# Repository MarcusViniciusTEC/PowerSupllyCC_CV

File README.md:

# PowerSupllyCC_CV

layout fonte CC/CV, controlado por STM32F103 e display 128x64

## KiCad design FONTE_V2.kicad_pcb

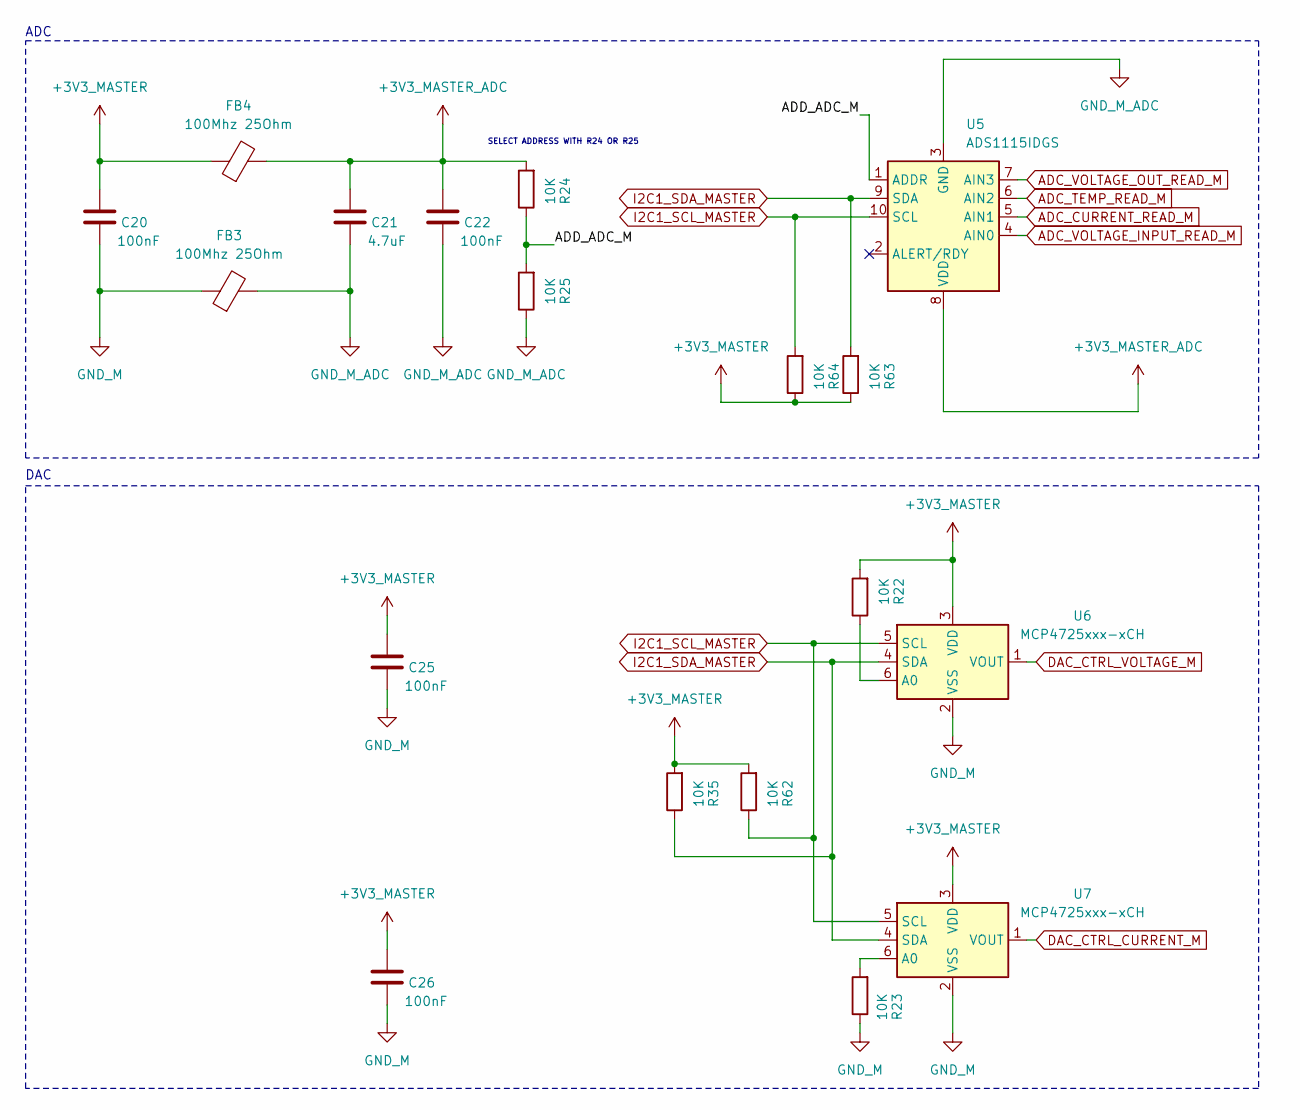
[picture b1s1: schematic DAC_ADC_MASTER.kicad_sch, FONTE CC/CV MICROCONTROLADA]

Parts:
C20, C22, C25, C26: 100nF; C_0805_2012Metric_Pad1.18x1.45mm_HandSolder
C21: 4.7uF; C_0805_2012Metric_Pad1.18x1.45mm_HandSolder
FB3, FB4: 100Mhz 25Ohm; L_0805_2012Metric_Pad1.15x1.40mm_HandSolder
R22, R23, R24, R25, R35, R62, R63, R64: 10K; R_0805_2012Metric_Pad1.20x1.40mm_HandSolder
U5: ADS1115IDGS; TSSOP-10_3x3mm_P0.5mm
U6, U7: MCP4725xxx-xCH; SOT-23-6

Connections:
+3V3_MASTER: C20.1, C25.1, C26.1, FB4.1, R22.2, R35.2, R62.2, R63.1, R64.1, U6.3 (VDD), U7.3 (VDD); also elsewhere on the board
+3V3_MASTER_ADC: C21.1, C22.1, FB4.2, R24.2, U5.8 (VDD)
/DAC_ADC_MASTER/ADD_ADC_M: R24.1, R25.2, U5.1 (ADDR)
ADC_CURRENT_READ_M: U5.5 (AIN1); also elsewhere on the board
ADC_TEMP_READ_M: U5.6 (AIN2); also elsewhere on the board
ADC_VOLTAGE_INPUT_READ_M: U5.4 (AIN0); also elsewhere on the board
ADC_VOLTAGE_OUT_READ_M: U5.7 (AIN3); also elsewhere on the board
DAC_CTRL_CURRENT_M: U7.1 (VOUT); also elsewhere on the board
DAC_CTRL_VOLTAGE_M: U6.1 (VOUT); also elsewhere on the board
GND_M_ADC: C21.2, C22.2, FB3.2, R25.1, U5.3 (GND)
I2C1_SCL_MASTER: R62.1, R64.2, U5.10 (SCL), U6.5 (SCL), U7.5 (SCL); also elsewhere on the board
I2C1_SDA_MASTER: R35.1, R63.2, U5.9 (SDA), U6.4 (SDA), U7.4 (SDA); also elsewhere on the board
unnamed: R22.1, U6.6 (A0)
unnamed: R23.2, U7.6 (A0)

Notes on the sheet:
SELECT ADDRESS WITH R24 OR R25
ADC
DAC

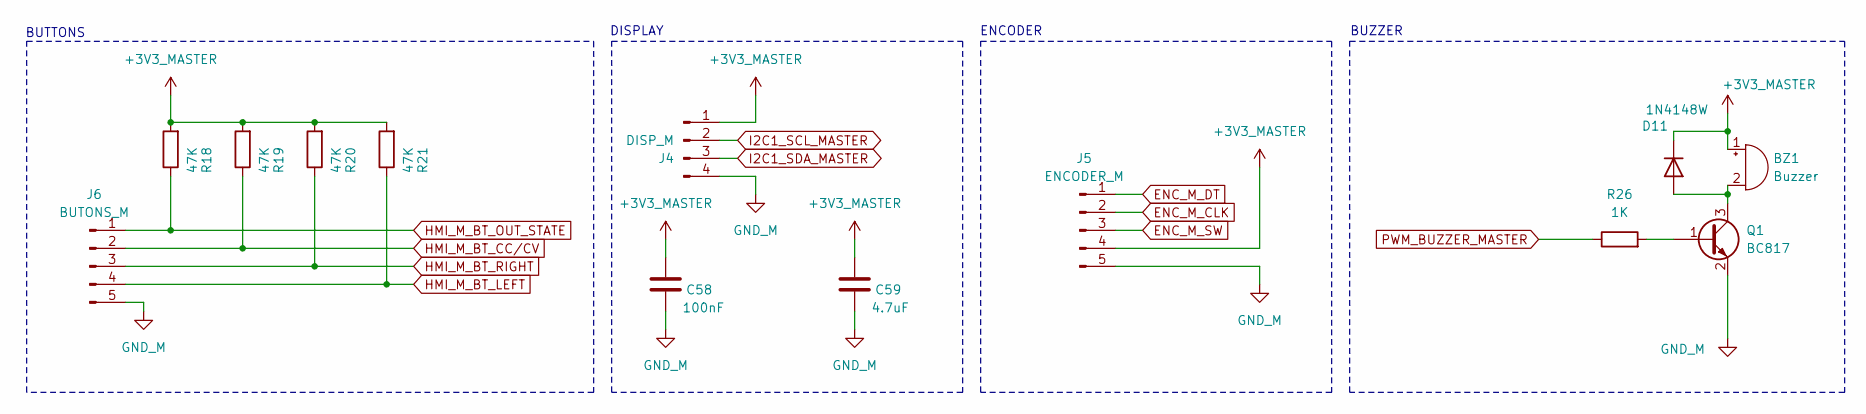
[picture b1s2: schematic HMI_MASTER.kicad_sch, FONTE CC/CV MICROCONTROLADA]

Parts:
BZ1: Buzzer; Buzzer_12x9.5RM7.6
C58: 100nF; C_0805_2012Metric_Pad1.18x1.45mm_HandSolder
C59: 4.7uF; C_0805_2012Metric_Pad1.18x1.45mm_HandSolder
D11: 1N4148W; D_SOD-123
J4: DISP_M; PinSocket_1x04_P2.54mm_Vertical
J5: ENCODER_M; PinHeader_1x05_P2.54mm_Vertical
J6: BUTONS_M; PinHeader_1x05_P2.54mm_Vertical
Q1: BC817; SOT-23
R18, R19, R20, R21: 47K; R_0805_2012Metric_Pad1.20x1.40mm_HandSolder
R26: 1K; R_0805_2012Metric

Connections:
+3V3_MASTER: BZ1.1 (+), C58.1, C59.1, D11.1 (K), J4.1, J5.4, R18.2, R19.2, R20.2, R21.2; also elsewhere on the board
ENC_M_CLK: J5.2; also elsewhere on the board
ENC_M_DT: J5.1; also elsewhere on the board
ENC_M_SW: J5.3; also elsewhere on the board
HMI_M_BT_CC/CV: J6.2, R19.1; also elsewhere on the board
HMI_M_BT_LEFT: J6.4, R21.1; also elsewhere on the board
HMI_M_BT_OUT_STATE: J6.1, R18.1; also elsewhere on the board
HMI_M_BT_RIGHT: J6.3, R20.1; also elsewhere on the board
I2C1_SCL_MASTER: J4.2; also elsewhere on the board
I2C1_SDA_MASTER: J4.3; also elsewhere on the board
unnamed: BZ1.2 (-), D11.2 (A), Q1.3 (C)
unnamed: Q1.1 (B), R26.2
PWM_BUZZER_MASTER: R26.1; also elsewhere on the board

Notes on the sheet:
BUZZER
DISPLAY
BUTTONS
ENCODER

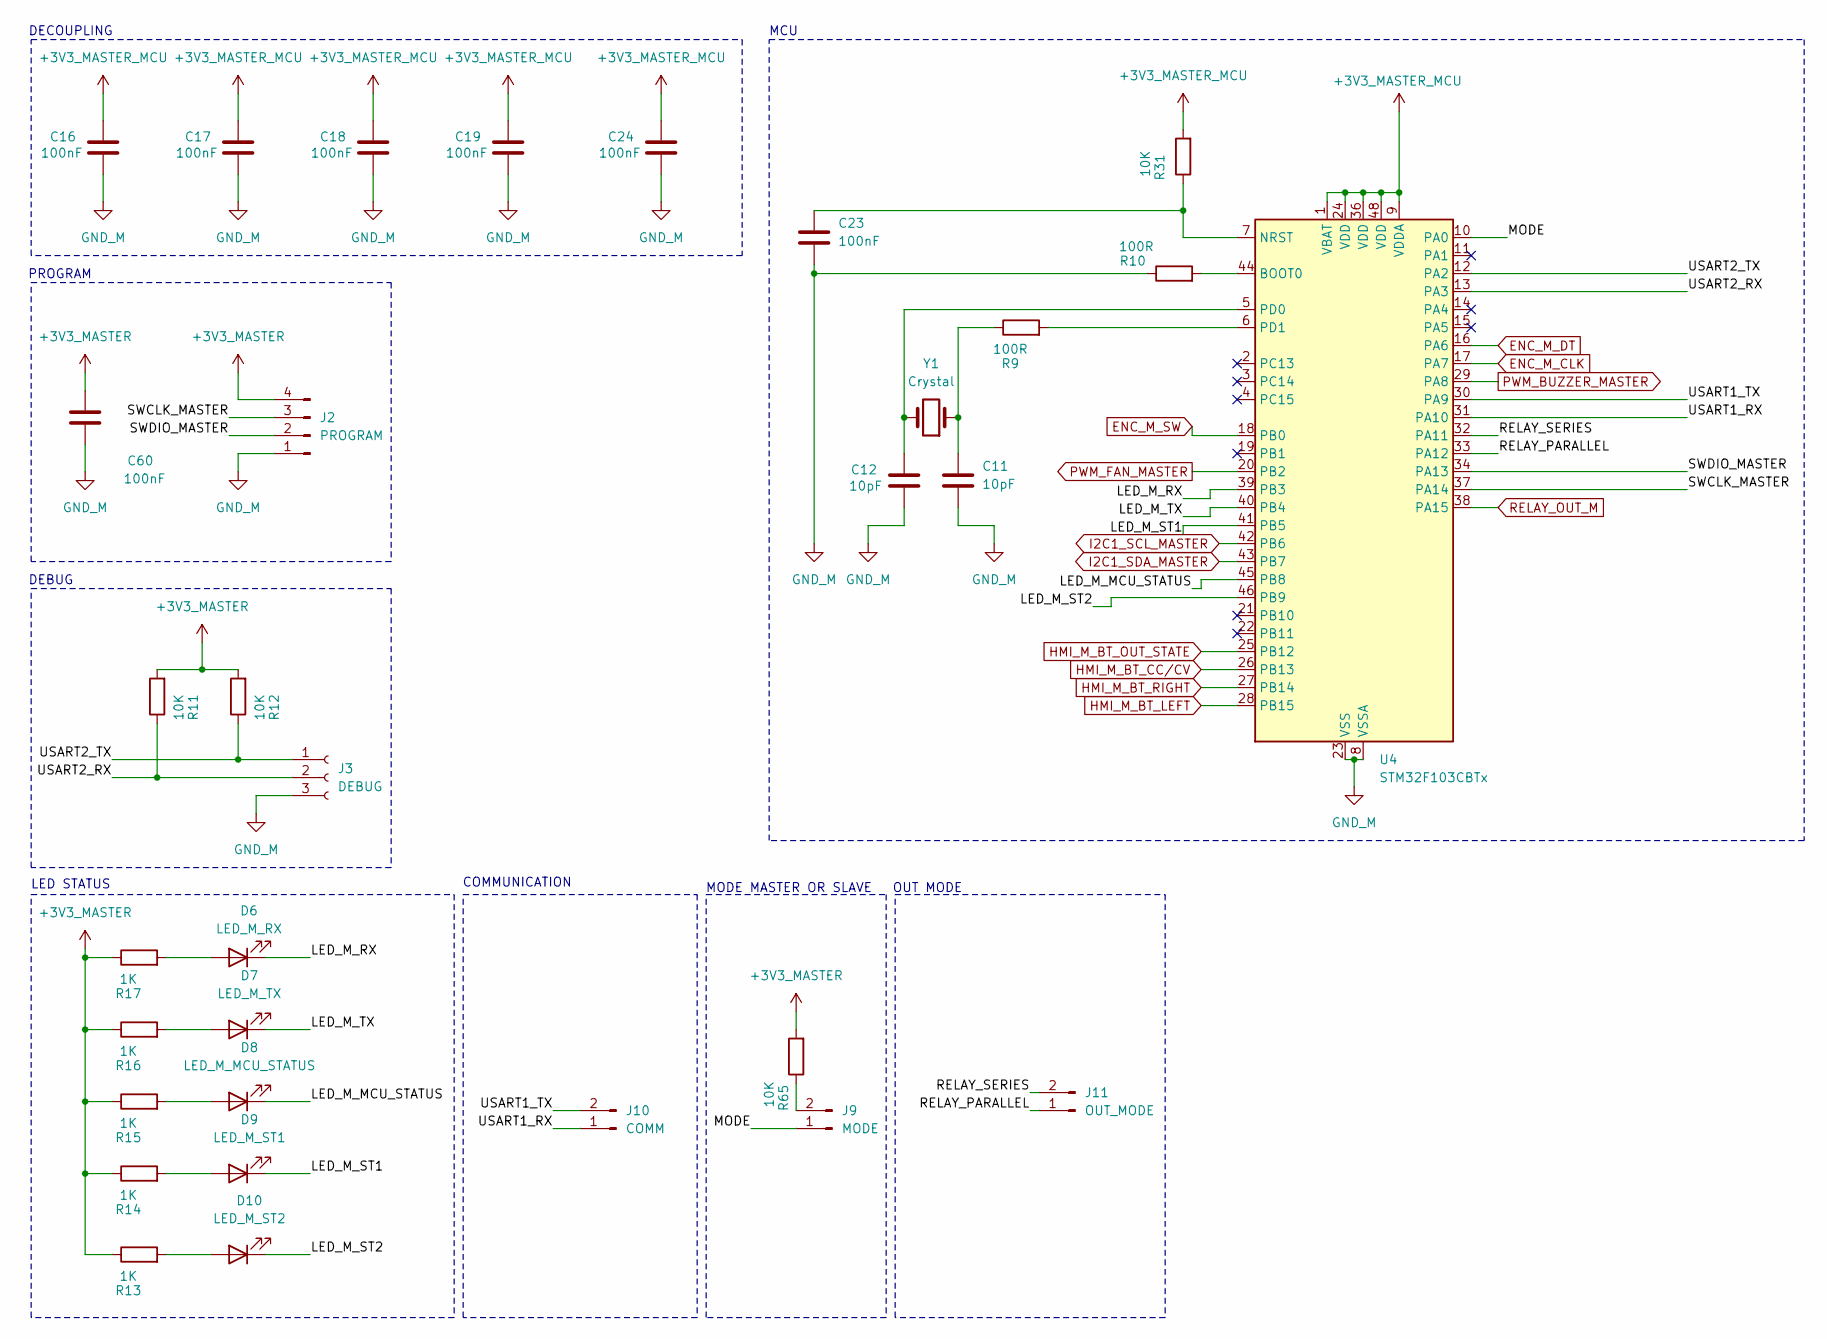
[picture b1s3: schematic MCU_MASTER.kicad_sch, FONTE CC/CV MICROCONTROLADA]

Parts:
C11, C12: 10pF; C_0805_2012Metric_Pad1.18x1.45mm_HandSolder
C16, C17, C18, C19, C23, C24, C60: 100nF; C_0805_2012Metric_Pad1.18x1.45mm_HandSolder
D6: LED_M_RX; LED_0805_2012Metric_Pad1.15x1.40mm_HandSolder
D7: LED_M_TX; LED_0805_2012Metric_Pad1.15x1.40mm_HandSolder
D8: LED_M_MCU_STATUS; LED_0805_2012Metric_Pad1.15x1.40mm_HandSolder
D9: LED_M_ST1; LED_0805_2012Metric_Pad1.15x1.40mm_HandSolder
D10: LED_M_ST2; LED_0805_2012Metric_Pad1.15x1.40mm_HandSolder
J2: PROGRAM; PinSocket_1x04_P2.54mm_Vertical
J3: DEBUG; PinHeader_1x03_P2.54mm_Vertical
J9: MODE; PinHeader_1x02_P2.54mm_Vertical
J10: COMM; PinHeader_1x02_P2.54mm_Vertical
J11: OUT_MODE; PinHeader_1x02_P2.54mm_Vertical
R9: 100R; R_0805_2012Metric_Pad1.20x1.40mm_HandSolder
R10: 100R; R_0805_2012Metric
R11, R12: 10K; R_0805_2012Metric_Pad1.20x1.40mm_HandSolder
R13, R14, R15, R16, R17: 1K; R_0805_2012Metric_Pad1.20x1.40mm_HandSolder
R31, R65: 10K; R_0805_2012Metric
U4: STM32F103CBTx; LQFP-48_7x7mm_P0.5mm
Y1: Crystal; Crystal_SMD_HC49-SD

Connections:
+3V3_MASTER: C60.1, J2.4, R11.2, R12.2, R13.1, R14.1, R15.1, R16.1, R17.1, R65.2; also elsewhere on the board
+3V3_MASTER_MCU: C16.1, C17.1, C18.1, C19.1, C24.1, R31.2, U4.1 (VBAT), U4.9 (VDDA), U4.24 (VDD), U4.36 (VDD), U4.48 (VDD); also elsewhere on the board
/MCU_MASTER/LED_M_MCU_STATUS: D8.1 (K), U4.45 (PB8)
/MCU_MASTER/LED_M_RX: D6.1 (K), U4.39 (PB3)
/MCU_MASTER/LED_M_ST1: D9.1 (K), U4.41 (PB5)
/MCU_MASTER/LED_M_ST2: D10.1 (K), U4.46 (PB9)
/MCU_MASTER/LED_M_TX: D7.1 (K), U4.40 (PB4)
/MCU_MASTER/MODE: J9.1, U4.10 (PA0)
/MCU_MASTER/RELAY_PARALLEL: J11.1, U4.33 (PA12)
/MCU_MASTER/RELAY_SERIES: J11.2, U4.32 (PA11)
/MCU_MASTER/SWCLK_MASTER: J2.3, U4.37 (PA14)
/MCU_MASTER/SWDIO_MASTER: J2.2, U4.34 (PA13)
/MCU_MASTER/USART1_RX: J10.1, U4.31 (PA10)
/MCU_MASTER/USART1_TX: J10.2, U4.30 (PA9)
/MCU_MASTER/USART2_RX: J3.2, R11.1, U4.13 (PA3)
/MCU_MASTER/USART2_TX: J3.1, R12.1, U4.12 (PA2)
ENC_M_CLK: U4.17 (PA7); also elsewhere on the board
ENC_M_DT: U4.16 (PA6); also elsewhere on the board
ENC_M_SW: U4.18 (PB0); also elsewhere on the board
HMI_M_BT_CC/CV: U4.26 (PB13); also elsewhere on the board
HMI_M_BT_LEFT: U4.28 (PB15); also elsewhere on the board
HMI_M_BT_OUT_STATE: U4.25 (PB12); also elsewhere on the board
HMI_M_BT_RIGHT: U4.27 (PB14); also elsewhere on the board
I2C1_SCL_MASTER: U4.42 (PB6); also elsewhere on the board
I2C1_SDA_MASTER: U4.43 (PB7); also elsewhere on the board
unnamed: C11.1, R9.1, Y1.1
unnamed: D6.2 (A), R17.2
unnamed: D7.2 (A), R16.2
unnamed: D8.2 (A), R15.2
unnamed: D9.2 (A), R14.2
unnamed: D10.2 (A), R13.2
unnamed: J9.2, R65.1
unnamed: R10.2, U4.44 (BOOT0)
unnamed: C12.1, U4.5 (PD0), Y1.2
unnamed: R9.2, U4.6 (PD1)
PWM_BUZZER_MASTER: U4.29 (PA8); also elsewhere on the board
PWM_FAN_MASTER: U4.20 (PB2); also elsewhere on the board
RELAY_OUT_M: U4.38 (PA15); also elsewhere on the board

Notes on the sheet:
MODE MASTER OR SLAVE
DECOUPLING
OUT MODE
LED STATUS
PROGRAM
DEBUG
MCU
COMMUNICATION

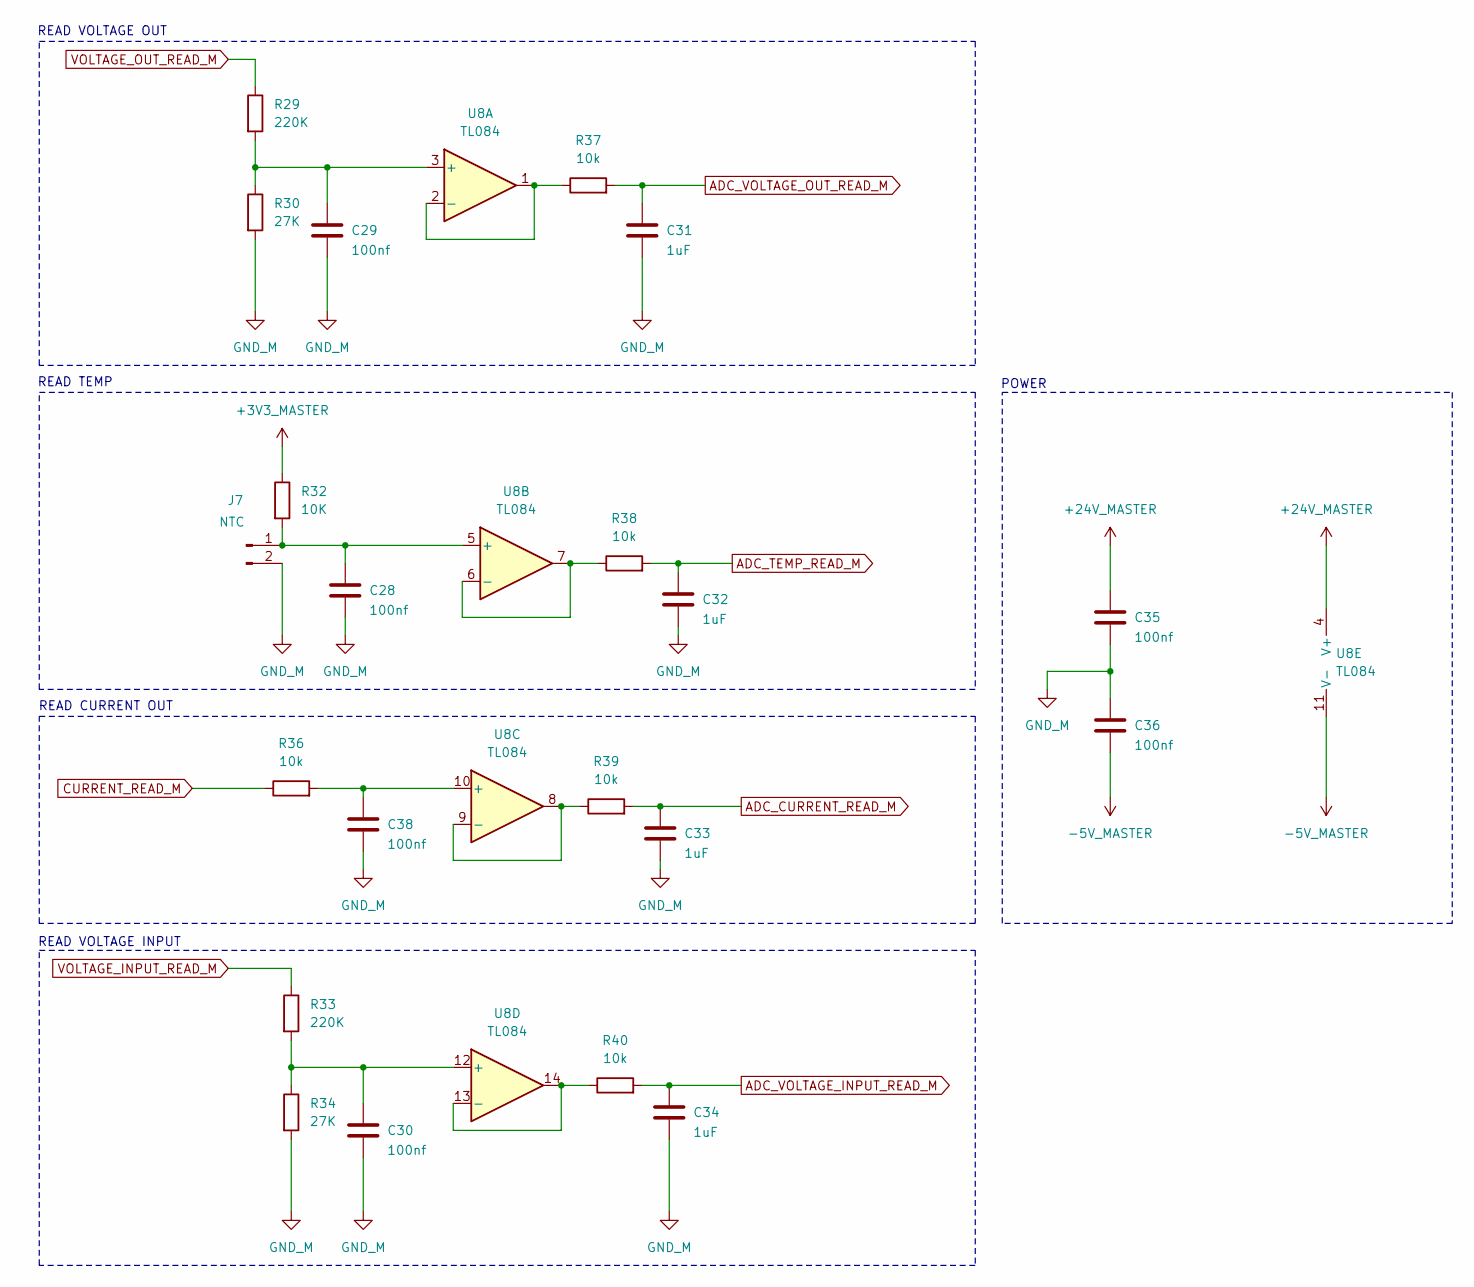
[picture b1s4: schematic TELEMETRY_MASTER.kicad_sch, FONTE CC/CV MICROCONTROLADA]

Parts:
C28, C29, C30, C35, C36, C38: 100nf; C_0805_2012Metric
C31, C32, C33, C34: 1uF; C_0805_2012Metric
J7: NTC; PinSocket_1x02_P2.54mm_Vertical
R29, R33: 220K; R_0805_2012Metric
R30, R34: 27K; R_0805_2012Metric
R32: 10K; R_0805_2012Metric
R36, R37, R38, R39, R40: 10k; R_0805_2012Metric
U8: TL084; SOIC-14_3.9x8.7mm_P1.27mm

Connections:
+3V3_MASTER: R32.1; also elsewhere on the board
-5V_MASTER: C36.2, U8.11 (V-); also elsewhere on the board
ADC_CURRENT_READ_M: C33.1, R39.2; also elsewhere on the board
ADC_TEMP_READ_M: C32.1, R38.2; also elsewhere on the board
ADC_VOLTAGE_INPUT_READ_M: C34.1, R40.2; also elsewhere on the board
ADC_VOLTAGE_OUT_READ_M: C31.1, R37.2; also elsewhere on the board
CURRENT_READ_M: R36.1; also elsewhere on the board
unnamed: C28.1, J7.1, R32.2, U8.5 (+)
unnamed: C29.1, R29.2, R30.1, U8.3 (+)
unnamed: R37.1, U8.1, U8.2 (-)
unnamed: R38.1, U8.6 (-), U8.7
unnamed: C38.1, R36.2, U8.10 (+)
unnamed: R39.1, U8.8, U8.9 (-)
unnamed: C30.1, R33.2, R34.1, U8.12 (+)
unnamed: R40.1, U8.13 (-), U8.14
VOLTAGE_INPUT_READ_M: C35.1, R33.1, U8.4 (V+); also elsewhere on the board
VOLTAGE_OUT_READ_M: R29.1; also elsewhere on the board

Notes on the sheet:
READ VOLTAGE OUT
POWER
READ TEMP
READ VOLTAGE INPUT
READ CURRENT OUT

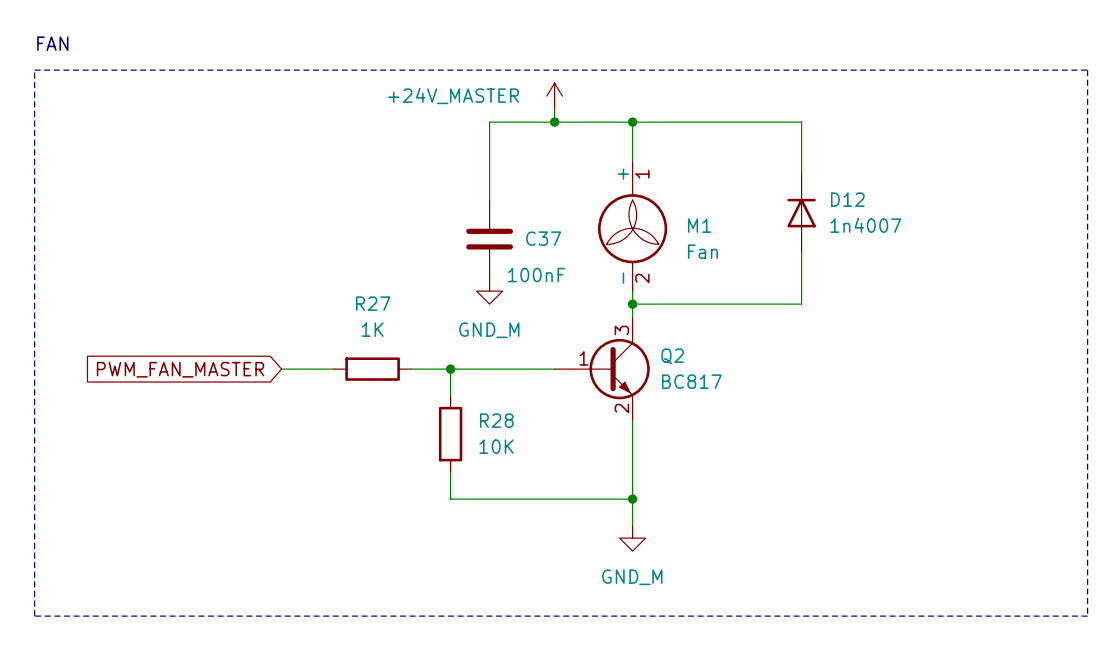
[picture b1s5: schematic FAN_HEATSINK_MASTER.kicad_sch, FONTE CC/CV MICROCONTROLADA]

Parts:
C37: 100nF; C_0805_2012Metric_Pad1.18x1.45mm_HandSolder
D12: 1n4007; D_SMA_Handsoldering
M1: Fan; PinHeader_1x02_P2.54mm_Vertical
Q2: BC817; SOT-23
R27: 1K; R_0805_2012Metric
R28: 10K; R_0805_2012Metric

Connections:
unnamed: D12.2 (A), M1.2 (-), Q2.3 (C)
unnamed: Q2.1 (B), R27.1, R28.1
PWM_FAN_MASTER: R27.2; also elsewhere on the board
VOLTAGE_INPUT_READ_M: C37.1, D12.1 (K), M1.1 (+); also elsewhere on the board

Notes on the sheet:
FAN

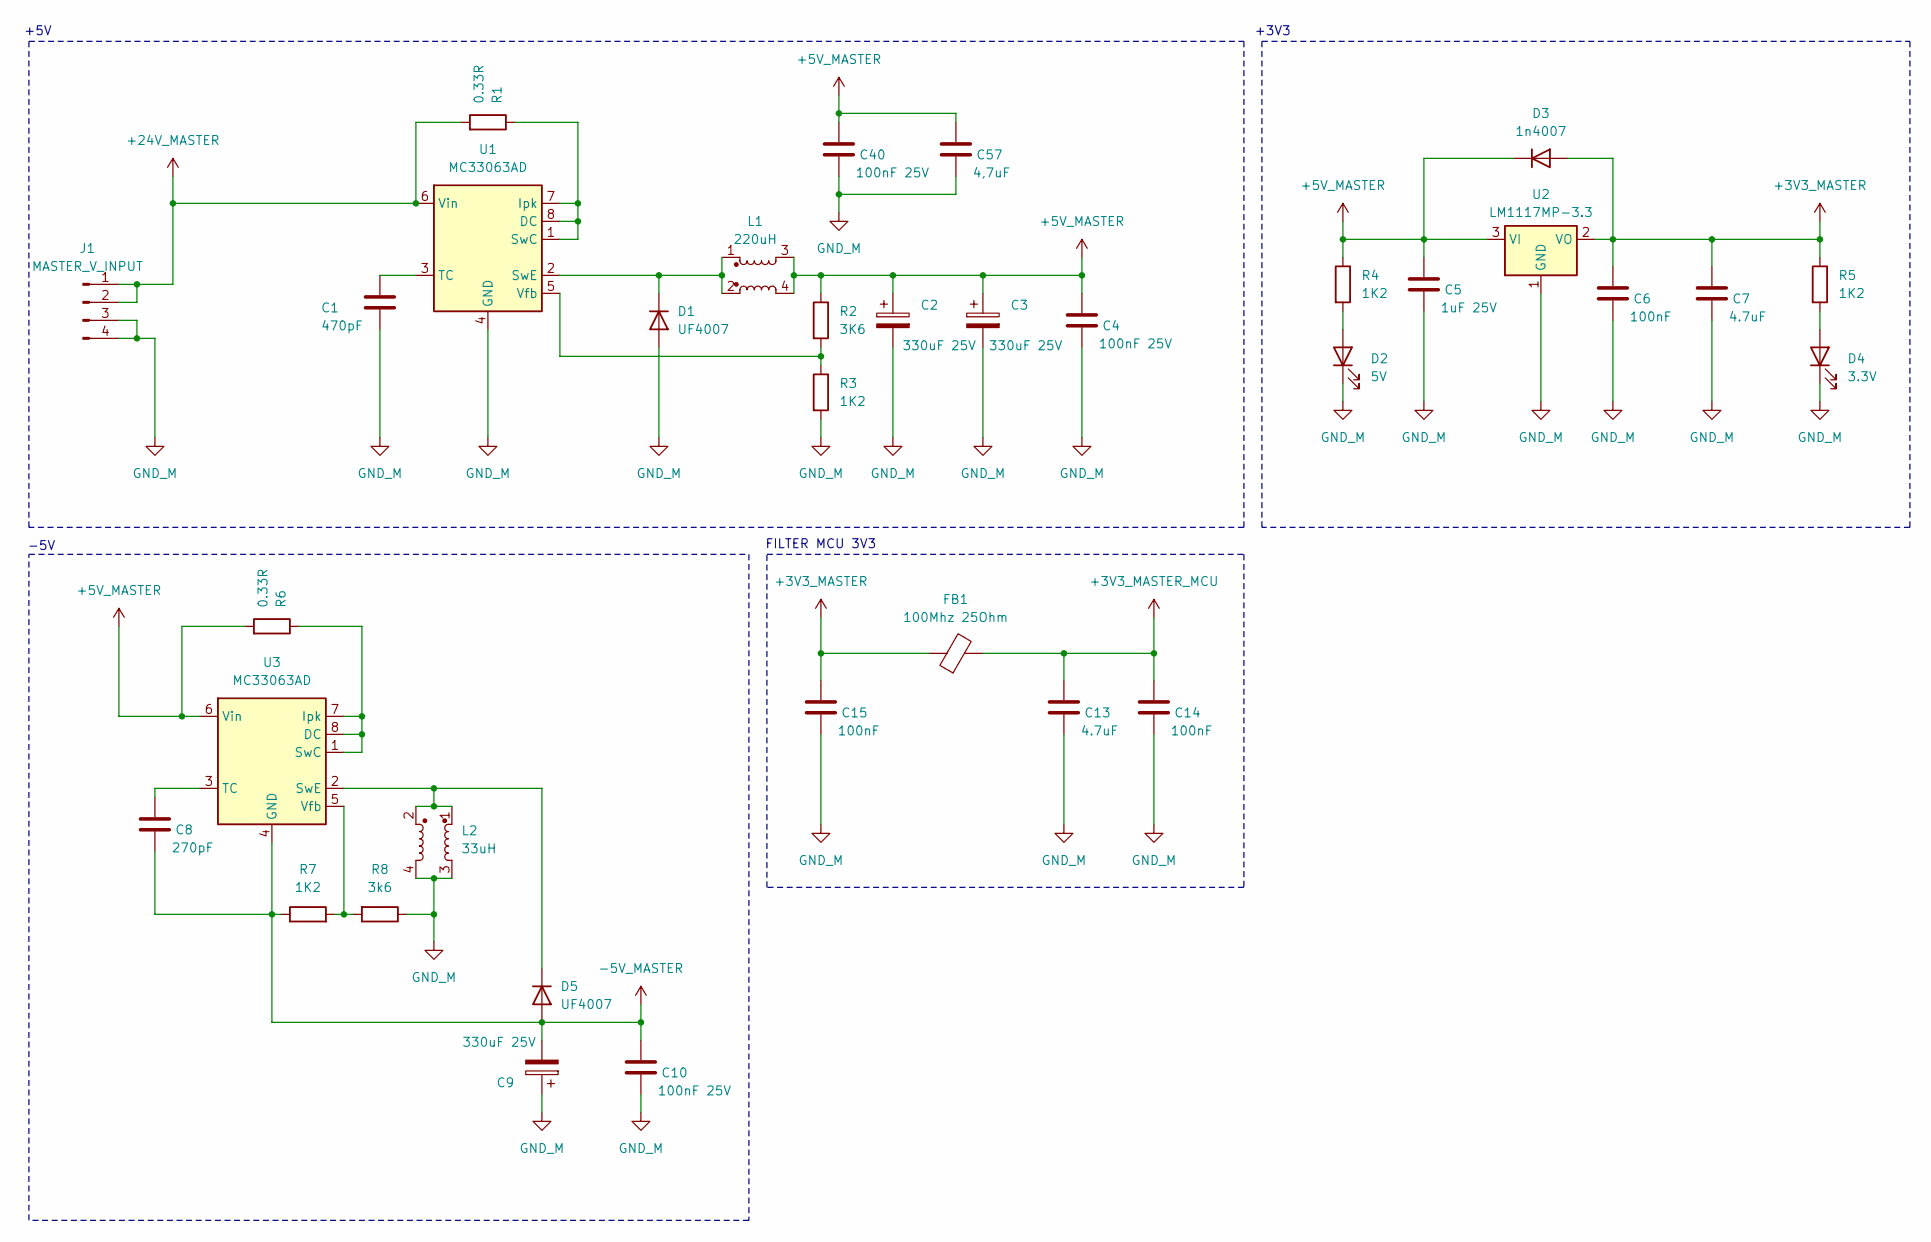
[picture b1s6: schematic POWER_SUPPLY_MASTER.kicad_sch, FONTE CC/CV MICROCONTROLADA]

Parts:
C1: 470pF; C_0805_2012Metric_Pad1.18x1.45mm_HandSolder
C2, C3, C9: 330uF 25V; CP_Radial_D8.0mm_P3.50mm
C4, C10, C40: 100nF 25V; C_0805_2012Metric_Pad1.18x1.45mm_HandSolder
C5: 1uF 25V; C_0805_2012Metric_Pad1.18x1.45mm_HandSolder
C6, C14, C15: 100nF; C_0805_2012Metric_Pad1.18x1.45mm_HandSolder
C7, C13: 4.7uF; C_0805_2012Metric_Pad1.18x1.45mm_HandSolder
C8: 270pF; C_0805_2012Metric_Pad1.18x1.45mm_HandSolder
C57: 4,7uF; C_0805_2012Metric_Pad1.18x1.45mm_HandSolder
D1, D5: UF4007; D_DO-41_SOD81_P10.16mm_Horizontal
D2: 5V; LED_0805_2012Metric
D3: 1n4007; D_SMA_Handsoldering
D4: 3.3V; LED_0805_2012Metric
FB1: 100Mhz 25Ohm; L_0805_2012Metric_Pad1.15x1.40mm_HandSolder
J1: MASTER_V_INPUT; PhoenixContact_MSTBVA_2,5_4-G-5,08_1x04_P5.08mm_Vertical
L1: 220uH; L_Bourns_SRF1260
L2: 33uH; L_Bourns_SRF1260
R1, R6: 0.33R; R_Axial_DIN0207_L6.3mm_D2.5mm_P10.16mm_Horizontal
R2: 3K6; R_0805_2012Metric_Pad1.20x1.40mm_HandSolder
R3, R4, R5, R7: 1K2; R_0805_2012Metric_Pad1.20x1.40mm_HandSolder
R8: 3k6; R_0805_2012Metric_Pad1.20x1.40mm_HandSolder
U1, U3: MC33063AD; SOIC-8_3.9x4.9mm_P1.27mm
U2: LM1117MP-3.3; TO-252-3_TabPin2

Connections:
+3V3_MASTER: C6.1, C7.1, C15.1, D3.2 (A), FB1.1, R5.1, U2.2 (VO); also elsewhere on the board
+3V3_MASTER_MCU: C13.1, C14.1, FB1.2; also elsewhere on the board
+5V_MASTER: C2.1, C3.1, C4.1, C5.1, C40.1, C57.1, D3.1 (K), L1.3, L1.4, R2.1, R4.1, R6.2, U2.3 (VI), U3.6 (Vin); also elsewhere on the board
-5V_MASTER: C8.2, C9.2, C10.1, D5.2 (A), R7.1, U3.4 (GND); also elsewhere on the board
unnamed: D1.1 (K), L1.1, L1.2, U1.2 (SwE)
unnamed: D2.2 (A), R4.2
unnamed: D4.2 (A), R5.2
unnamed: D5.1 (K), L2.1, L2.2, U3.2 (SwE)
unnamed: R1.1, U1.1 (SwC), U1.7 (Ipk), U1.8 (DC)
unnamed: C1.1, U1.3 (TC)
unnamed: R2.2, R3.1, U1.5 (Vfb)
unnamed: R6.1, U3.1 (SwC), U3.7 (Ipk), U3.8 (DC)
unnamed: C8.1, U3.3 (TC)
unnamed: R7.2, R8.2, U3.5 (Vfb)
VOLTAGE_INPUT_READ_M: J1.1, J1.2, R1.2, U1.6 (Vin); also elsewhere on the board

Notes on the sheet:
FILTER MCU 3V3
+5V
+3V3
-5V

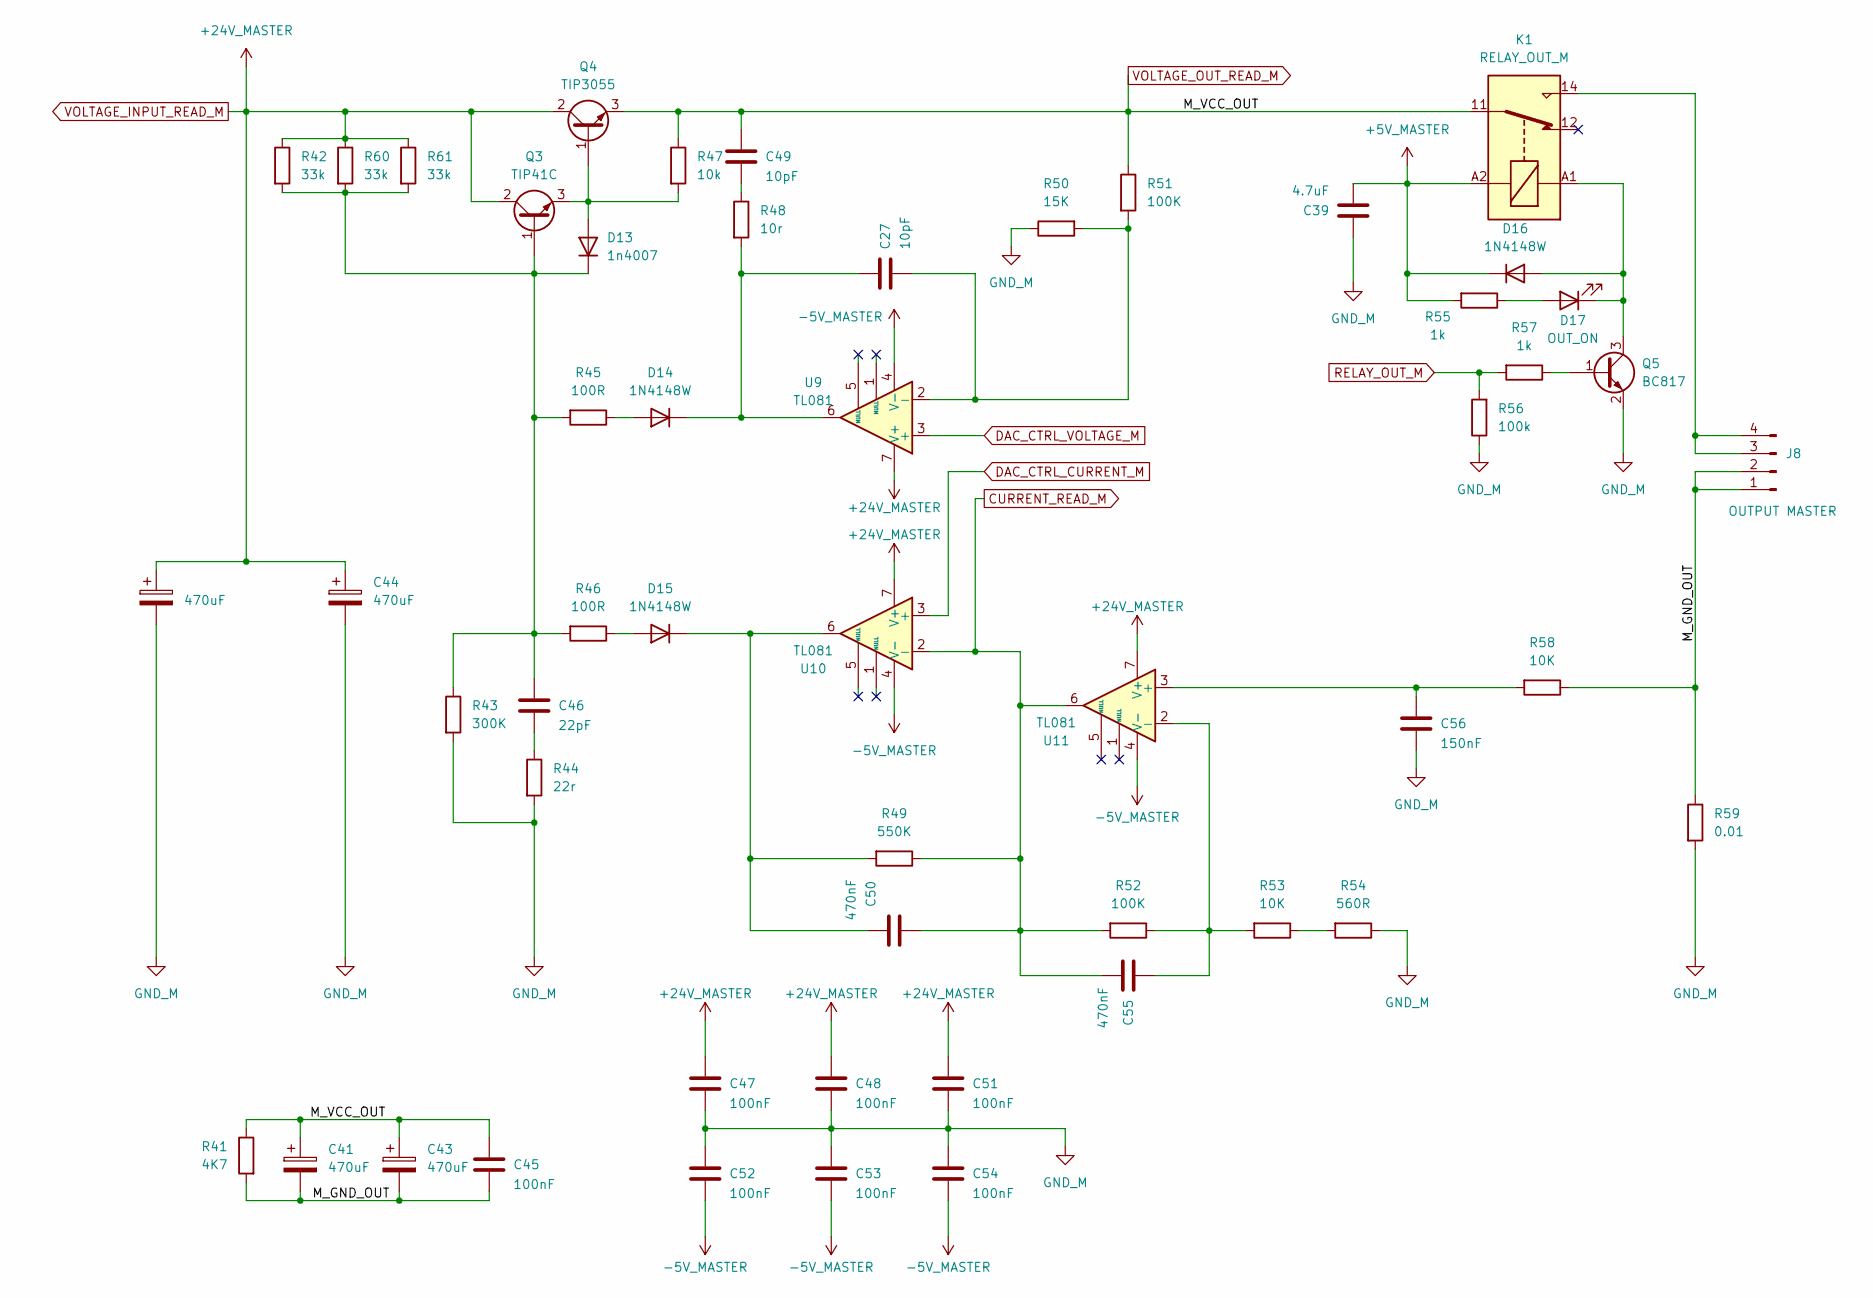
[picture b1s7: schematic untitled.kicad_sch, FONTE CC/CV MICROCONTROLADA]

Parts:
C27, C49: 10pF; C_0805_2012Metric
C39: 4.7uF; C_0805_2012Metric
C41, C42, C43, C44: 470uF; CP_Radial_D10.0mm_P5.00mm
C45, C47, C48, C51, C52, C53, C54: 100nF; C_0805_2012Metric
C46: 22pF; C_0805_2012Metric_Pad1.18x1.45mm_HandSolder
C50, C55: 470nF; C_0805_2012Metric_Pad1.18x1.45mm_HandSolder
C56: 150nF; C_0805_2012Metric_Pad1.18x1.45mm_HandSolder
D13: 1n4007; D_SMA_Handsoldering
D14, D15, D16: 1N4148W; D_SOD-123
D17: OUT_ON; LED_0805_2012Metric
J8: OUTPUT MASTER; PhoenixContact_MSTBVA_2,5_4-G-5,08_1x04_P5.08mm_Vertical
K1: RELAY_OUT_M; Relay_SPDT_Hongfa_HF3F-L-xx-1ZL1T
Q3: TIP41C; TO-220-3_Vertical
Q4: TIP3055; TO-218-3_Vertical
Q5: BC817; SOT-23
R41: 4K7; R_Axial_DIN0207_L6.3mm_D2.5mm_P10.16mm_Horizontal
R42, R60, R61: 33k; R_0805_2012Metric_Pad1.20x1.40mm_HandSolder
R43: 300K; R_0805_2012Metric_Pad1.20x1.40mm_HandSolder
R44: 22r; R_0805_2012Metric_Pad1.20x1.40mm_HandSolder
R45, R46: 100R; R_0805_2012Metric_Pad1.20x1.40mm_HandSolder
R47: 10k; R_0805_2012Metric_Pad1.20x1.40mm_HandSolder
R48: 10r; R_0805_2012Metric_Pad1.20x1.40mm_HandSolder
R49: 550K; R_0805_2012Metric_Pad1.20x1.40mm_HandSolder
R50: 15K; R_0805_2012Metric_Pad1.20x1.40mm_HandSolder
R51, R52: 100K; R_0805_2012Metric_Pad1.20x1.40mm_HandSolder
R53, R58: 10K; R_0805_2012Metric_Pad1.20x1.40mm_HandSolder
R54: 560R; R_0805_2012Metric_Pad1.20x1.40mm_HandSolder
R55: 1k; R_0805_2012Metric
R56: 100k; R_0805_2012Metric_Pad1.20x1.40mm_HandSolder
R57: 1k; R_0805_2012Metric_Pad1.20x1.40mm_HandSolder
R59: 0.01; R_2512_6332Metric_Pad1.40x3.35mm_HandSolder
U9, U10, U11: TL081; SOIC-8_3.9x4.9mm_P1.27mm

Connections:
+5V_MASTER: C39.2, D16.1 (K), K1.A2, R55.2; also elsewhere on the board
-5V_MASTER: C52.2, C53.2, C54.2, U9.4 (V-), U10.4 (V-), U11.4 (V-); also elsewhere on the board
/REG_POWER_SUPPLY/M_GND_OUT: C41.2, C43.2, C45.2, J8.1, J8.2, R41.2, R58.1, R59.1
CURRENT_READ_M: C50.1, C55.2, R49.1, R52.2, U10.2 (-), U11.6; also elsewhere on the board
DAC_CTRL_CURRENT_M: U10.3 (+); also elsewhere on the board
DAC_CTRL_VOLTAGE_M: U9.3 (+); also elsewhere on the board
unnamed: C46.2, R44.1
unnamed: C49.2, R48.1
unnamed: D13.2 (A), Q3.3 (E), Q4.1 (B), R47.2
unnamed: C46.1, D13.1 (K), Q3.1 (B), R42.2, R43.1, R45.2, R46.2, R60.2, R61.2
unnamed: D14.2 (A), R45.1
unnamed: C27.1, D14.1 (K), R48.2, U9.6
unnamed: D15.2 (A), R46.1
unnamed: C50.2, D15.1 (K), R49.2, U10.6
unnamed: D16.2 (A), D17.1 (K), K1.A1, Q5.3 (C)
unnamed: D17.2 (A), R55.1
unnamed: J8.3, J8.4, K1.14
unnamed: Q5.1 (B), R57.1
unnamed: R53.1, R54.2
unnamed: C27.2, R50.2, R51.2, U9.2 (-)
unnamed: C56.1, R58.2, U11.3 (+)
unnamed: C55.1, R52.1, R53.2, U11.2 (-)
RELAY_OUT_M: R56.2, R57.2; also elsewhere on the board
VOLTAGE_INPUT_READ_M: C42.1, C44.1, C47.1, C48.1, C51.1, Q3.2 (C), Q4.2 (C), R42.1, R60.1, R61.1, U9.7 (V+), U10.7 (V+), U11.7 (V+); also elsewhere on the board
VOLTAGE_OUT_READ_M: C41.1, C43.1, C45.1, C49.1, K1.11, Q4.3 (E), R41.1, R47.1, R51.1; also elsewhere on the board

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
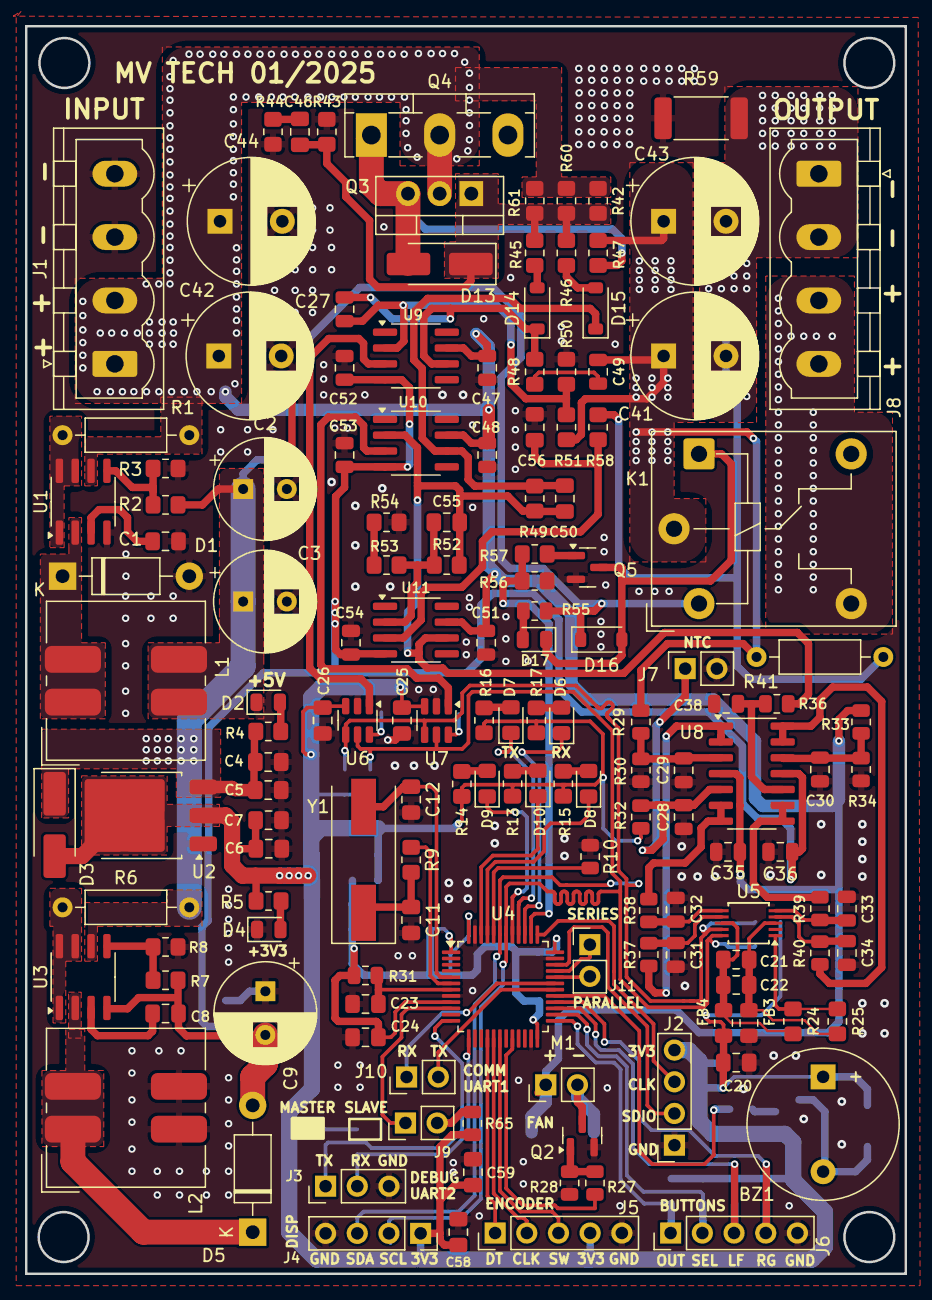
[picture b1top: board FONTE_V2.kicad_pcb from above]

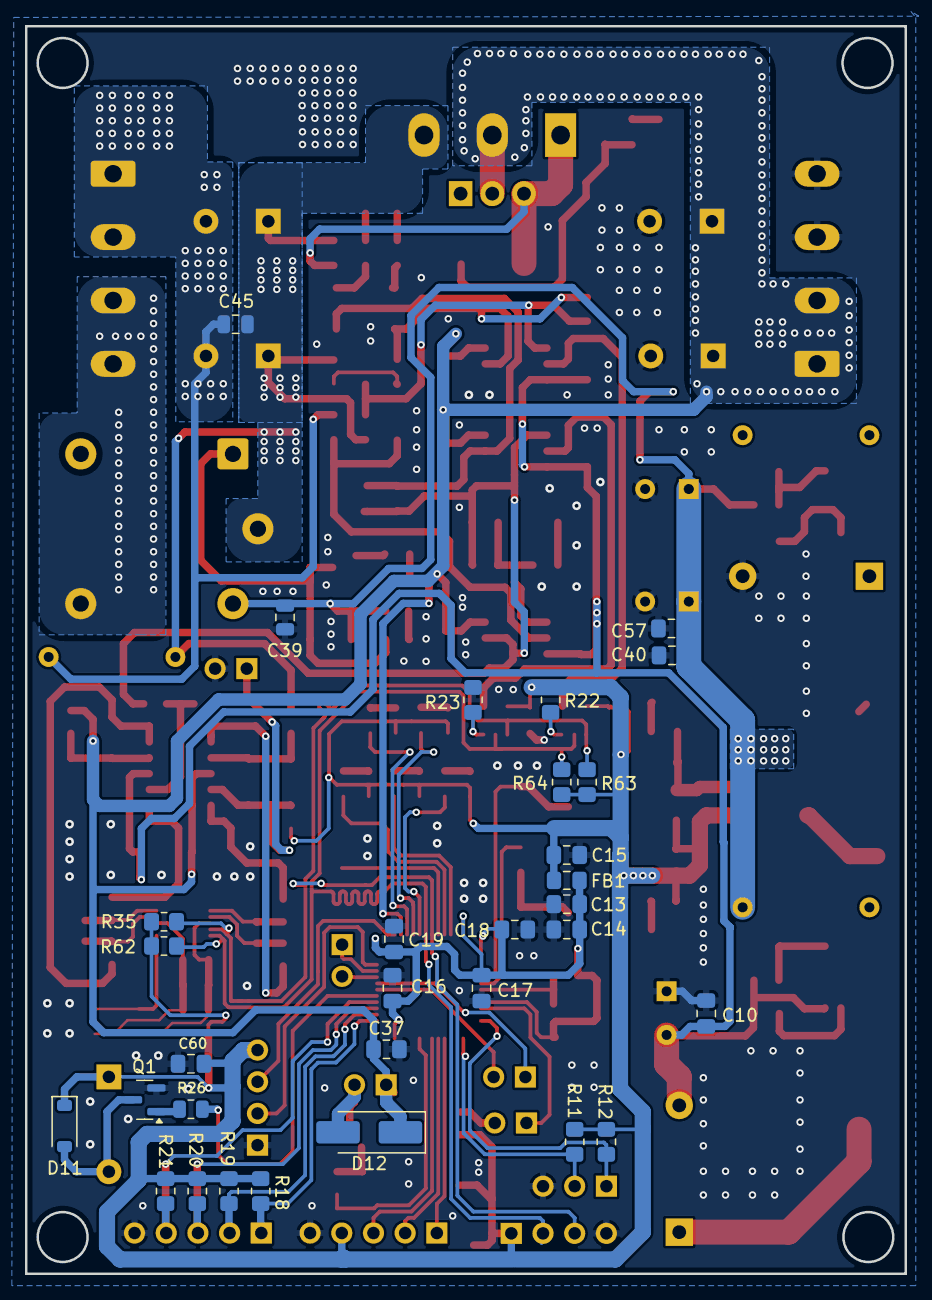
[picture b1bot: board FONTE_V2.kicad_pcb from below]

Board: 2 copper layers, 70.5 x 100.0 mm, 178 parts (31 on the bottom side), 95 nets.

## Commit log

2025-01-29 first version 0.1
